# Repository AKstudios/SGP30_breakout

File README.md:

# SGP30 Breakout
Breakout board for <a href="https://www.sensirion.com/en/environmental-sensors/gas-sensors/">Sensirion SGP30</a> Multipixel gas sensor.

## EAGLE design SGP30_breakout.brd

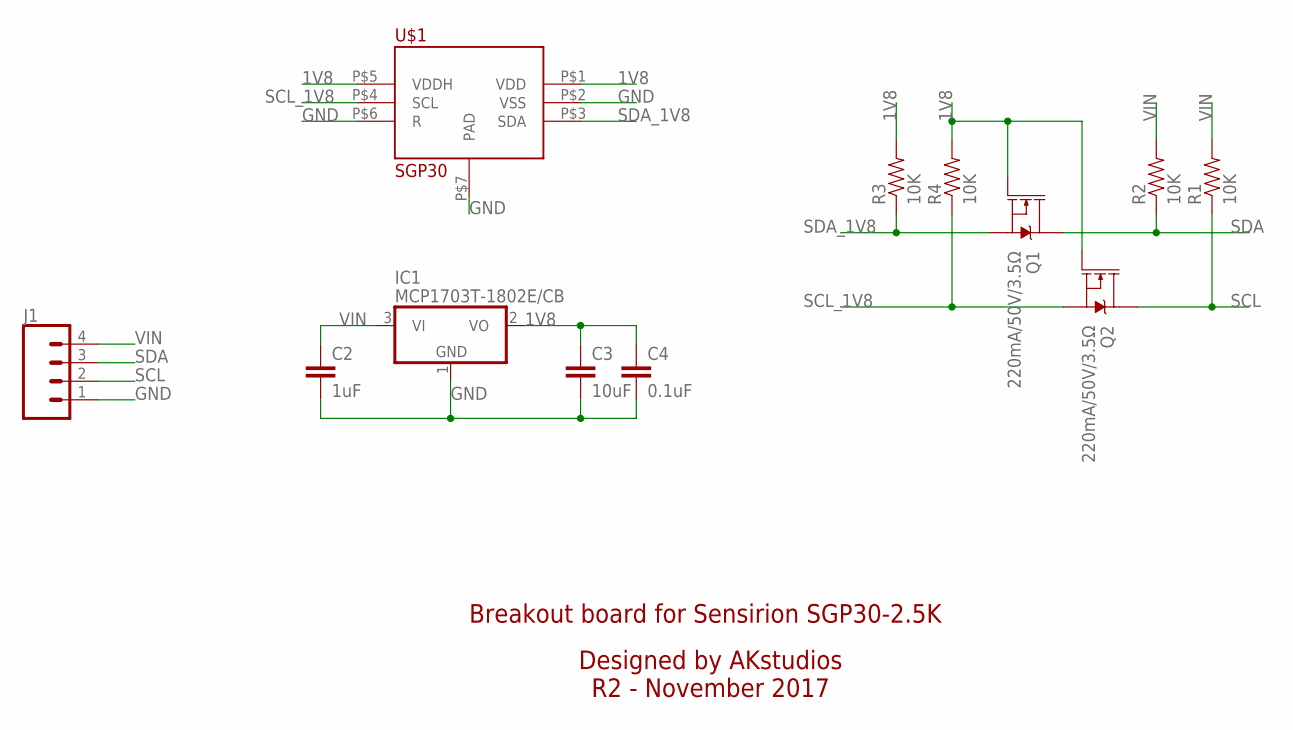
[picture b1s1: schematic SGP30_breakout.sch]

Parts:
C2: 1uF; 0805
C3: 10uF; 0805
C4: 0.1uF; 0805
IC1: MCP1703T-1802E/CB; SOT23
J1: CONN_04; 1X04
Q1, Q2: 220mA/50V/3.5Ω; SOT23-3
R1, R2, R3, R4: 10K; 0805
U$1: SGP30; DFN

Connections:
1V8: C3.1, C4.1, IC1.2 (VO), Q1.1 (G), Q2.1 (G), R3.2, R4.2, U$1.P$1 (VDD), U$1.P$5 (VDDH)
GND: C2.2, C3.2, C4.2, IC1.1 (GND), J1.1, U$1.P$2 (VSS), U$1.P$6 (R), U$1.P$7 (PAD)
SCL: J1.2, Q2.3 (D), R1.1
SCL_1V8: Q2.2 (S), R4.1, U$1.P$4 (SCL)
SDA: J1.3, Q1.3 (D), R2.1
SDA_1V8: Q1.2 (S), R3.1, U$1.P$3 (SDA)
VIN: C2.1, IC1.3 (VI), J1.4, R1.2, R2.2

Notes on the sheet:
Breakout board for Sensirion SGP30-2.5K
Designed by AKstudios R2 - November 2017

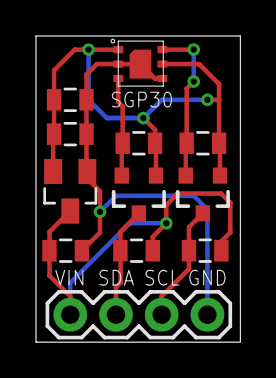
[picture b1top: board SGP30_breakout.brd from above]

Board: 2 copper layers, 11.4 x 17.0 mm, 12 parts (0 on the bottom side), 7 nets.

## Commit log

2017-10-24 :octocat: Added .gitattributes & .gitignore files
2017-10-24 init
2017-10-24 Added OSH park render
    renamed schematic file
2017-11-08 R2 - bug fixes
    - GND and SCL trace swapped
    - shrinked board size
    - silkscreen adjustments
    - removed GND plane
    - routed GND trace
    - trace adjustments
2017-11-08 rename sch

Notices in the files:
parts and their libraries:
SparkFun-Passives: Licensing: Creative Commons ShareAlike 4.0 International - https://creativecommons.org/licenses/by-sa/4.0
